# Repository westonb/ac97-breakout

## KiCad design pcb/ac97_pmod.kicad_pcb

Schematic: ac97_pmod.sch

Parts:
J101, J102, J103, J104: mounting-hole-nc; M3-small-mounting-hole

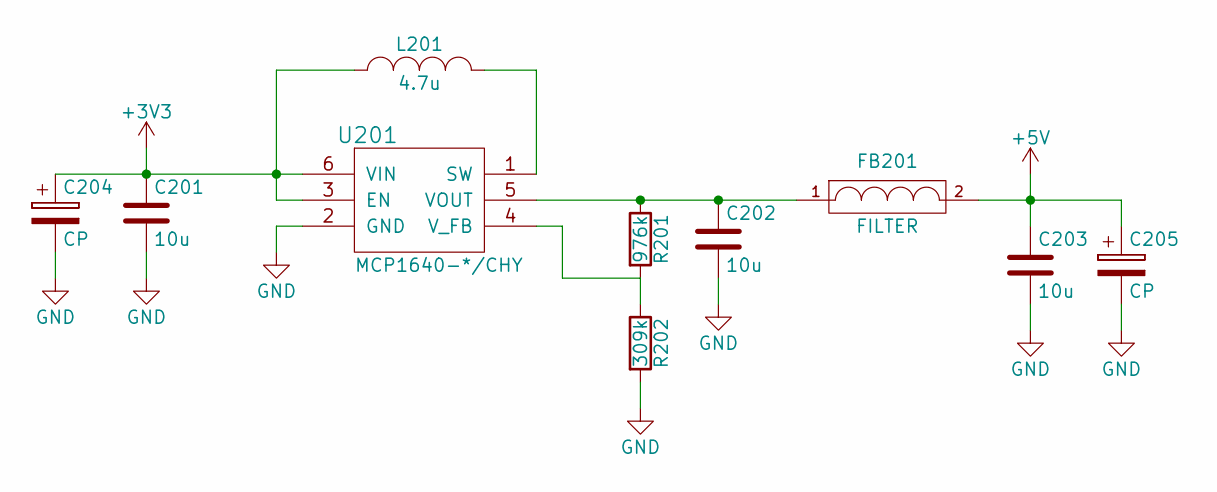
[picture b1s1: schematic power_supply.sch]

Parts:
C201, C202, C203: 10u; C_0805
C204, C205: CP; CP_Radial_D6.3mm_P2.50mm
FB201: FILTER; SMD-0805
L201: 4.7u; SMD-1008
R201: 976k; R_0805
R202: 309k; R_0805
U201: MCP1640-*/CHY; SOT-23-6

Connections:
+3V3: C201.1, C204.1, L201.1, U201.3 (EN), U201.6 (VIN); also elsewhere on the board
+5V: C203.1, C205.1, FB201.2; also elsewhere on the board
GND: C201.2, C202.2, C203.2, C204.2, C205.2, R202.2, U201.2 (GND); also elsewhere on the board
unnamed: C202.1, FB201.1, R201.1, U201.5 (VOUT)
unnamed: L201.2, U201.1 (SW)
unnamed: R201.2, R202.1, U201.4 (V_FB)

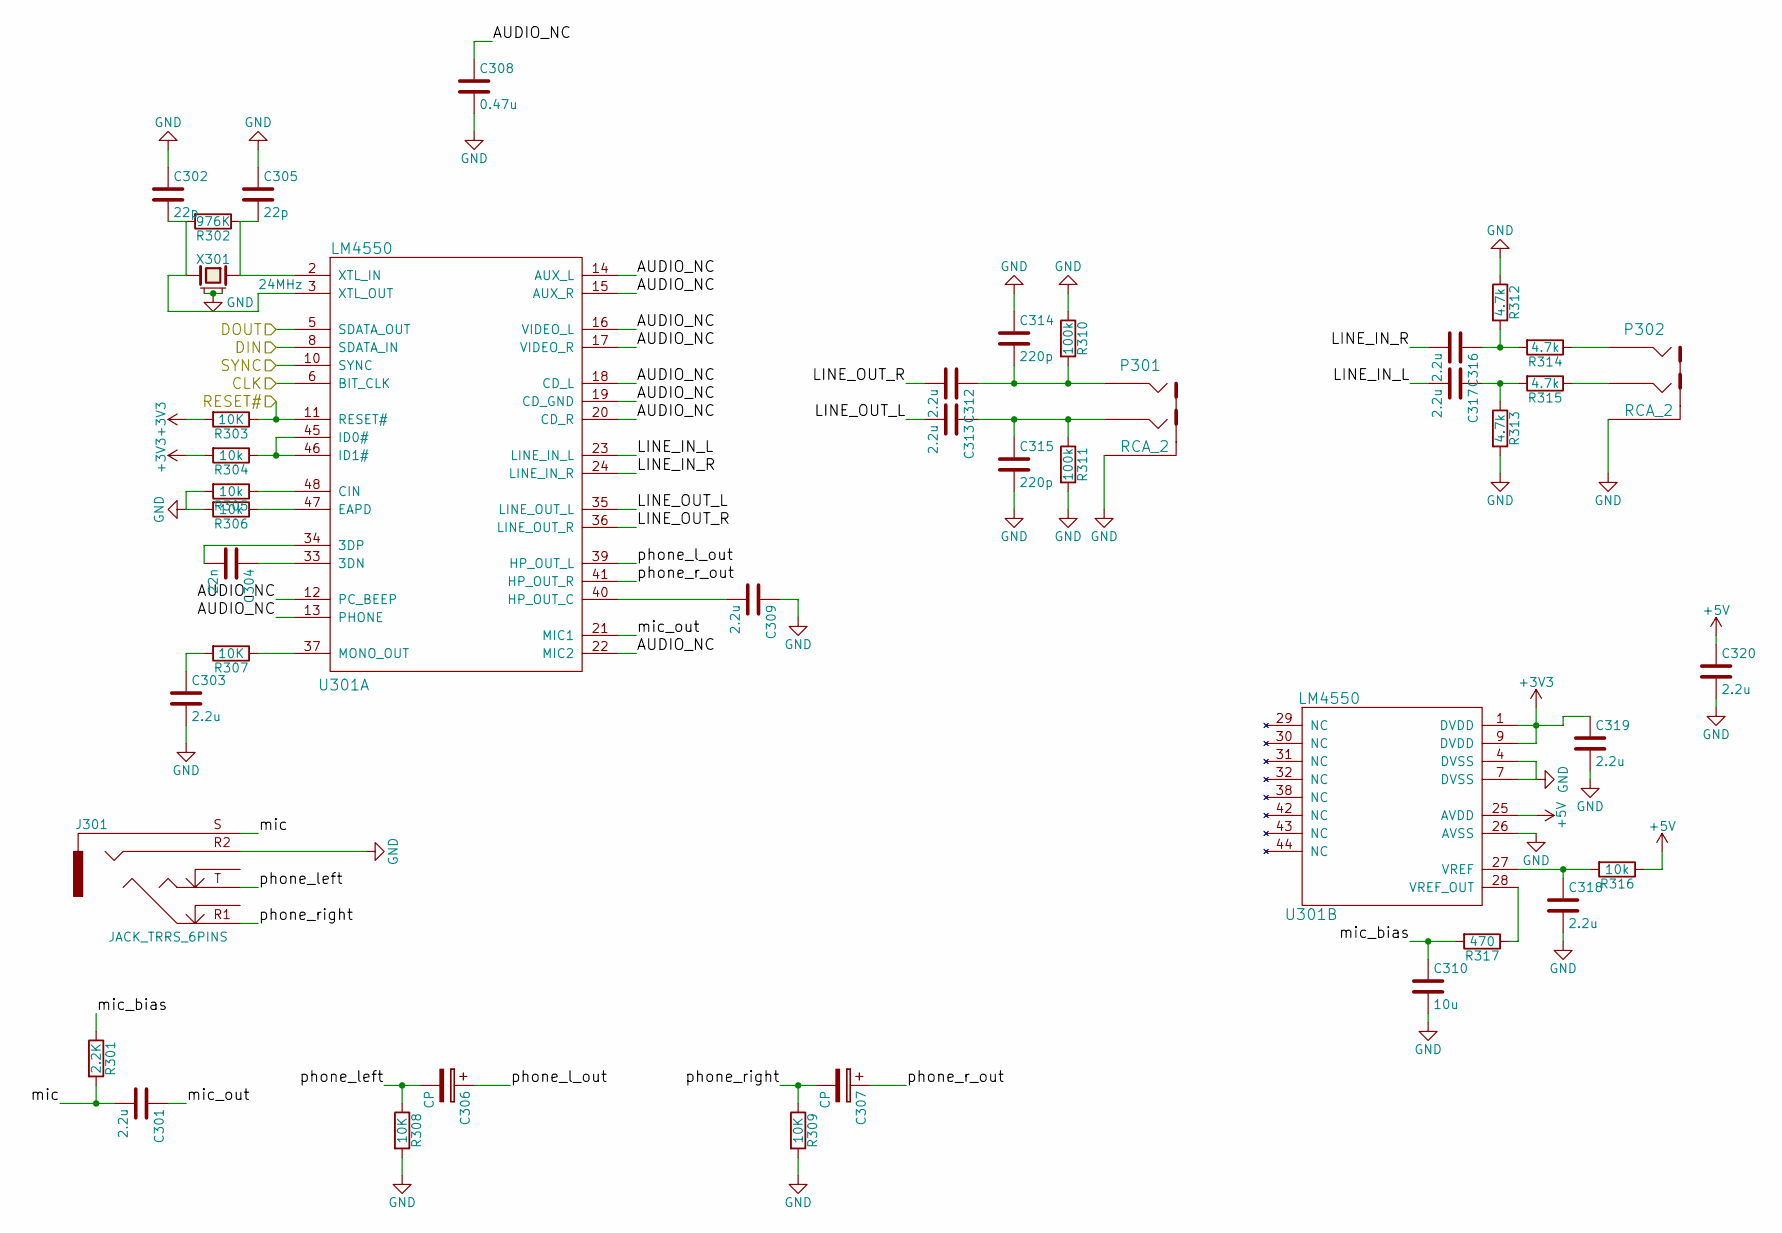
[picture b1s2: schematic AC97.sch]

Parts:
C301, C303, C309, C312, C313, C316, C317, C318, C319, C320: 2.2u; C_0805
C302, C305: 22p; C_0805
C304: 22n; C_0805
C306, C307: CP; CP_Radial_D6.3mm_P2.50mm
C308: 0.47u; C_0805
C310: 10u; C_0805
C314, C315: 220p; C_0805
J301: JACK_TRRS_6PINS; SJ-4351_X-SMT
P301, P302: RCA_2; RCJ-222x
R301: 2.2K; R_0805
R302: 976K; R_0805
R303, R307, R308, R309: 10K; R_0805
R304, R305, R306, R316: 10k; R_0805
R310, R311: 100k; R_0805
R312, R313, R314, R315: 4.7k; R_0805
R317: 470; R_0805
U301: LM4550; LQFP-48_7x7mm_Pitch0.5mm
X301: 24MHz; Crystal_6.0x3.6

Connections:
+3V3: C319.1, R303.2, R304.2, U301.1 (DVDD), U301.9 (DVDD); also elsewhere on the board
+5V: C320.1, R316.1, U301.25 (AVDD); also elsewhere on the board
/AC97/AUDIO_NC: C308.1, U301.12 (PC_BEEP), U301.13 (PHONE), U301.14 (AUX_L), U301.15 (AUX_R), U301.16 (VIDEO_L), U301.17 (VIDEO_R), U301.18 (CD_L), U301.19 (CD_GND), U301.20 (CD_R), U301.22 (MIC2)
/AC97/CLK: U301.6 (BIT_CLK); also elsewhere on the board
/AC97/DIN: U301.8 (SDATA_IN); also elsewhere on the board
/AC97/DOUT: U301.5 (SDATA_OUT); also elsewhere on the board
/AC97/LINE_IN_L: C317.2, U301.23 (LINE_IN_L)
/AC97/LINE_IN_R: C316.2, U301.24 (LINE_IN_R)
/AC97/LINE_OUT_L: C313.2, U301.35 (LINE_OUT_L)
/AC97/LINE_OUT_R: C312.2, U301.36 (LINE_OUT_R)
/AC97/SYNC: U301.10 (SYNC); also elsewhere on the board
/AC97/mic: C301.2, J301.1, R301.2
/AC97/mic_bias: C310.1, R301.1, R317.2
/AC97/mic_out: C301.1, U301.21 (MIC1)
/AC97/phone_l_out: C306.1, U301.39 (HP_OUT_L)
/AC97/phone_left: C306.2, J301.2, R308.1
/AC97/phone_r_out: C307.1, U301.41 (HP_OUT_R)
/AC97/phone_right: C307.2, J301.3, R309.1
/PMOD Connector/RESET: R303.1, U301.11 (RESET#); also elsewhere on the board
GND: C302.1, C303.2, C305.1, C308.2, C309.1, C310.2, C314.1, C315.2, C318.2, C319.2, C320.2, J301.4, P301.1, P302.1, R305.2, R306.2, R308.2, R309.2, R310.1, R311.2, R312.1, R313.2, U301.4 (DVSS), U301.7 (DVSS), U301.26 (AVSS), X301.2, X301.4; also elsewhere on the board
unnamed: C302.2, R302.2, U301.3 (XTL_OUT), X301.3
unnamed: C303.1, R307.2
unnamed: C304.1, U301.33 (3DN)
unnamed: C304.2, U301.34 (3DP)
unnamed: C305.2, R302.1, U301.2 (XTL_IN), X301.1
unnamed: C309.2, U301.40 (HP_OUT_C)
unnamed: C312.1, C314.2, P301.3, R310.2
unnamed: C313.1, C315.1, P301.2, R311.1
unnamed: C316.1, R312.2, R314.2
unnamed: C317.1, R313.1, R315.2
unnamed: C318.1, R316.2, U301.27 (VREF)
unnamed: P302.2, R315.1
unnamed: P302.3, R314.1
unnamed: R304.1, U301.45 (ID0#), U301.46 (ID1#)
unnamed: R305.1, U301.48 (CIN)
unnamed: R306.1, U301.47 (EAPD)
unnamed: R307.1, U301.37 (MONO_OUT)
unnamed: R317.1, U301.28 (VREF_OUT)

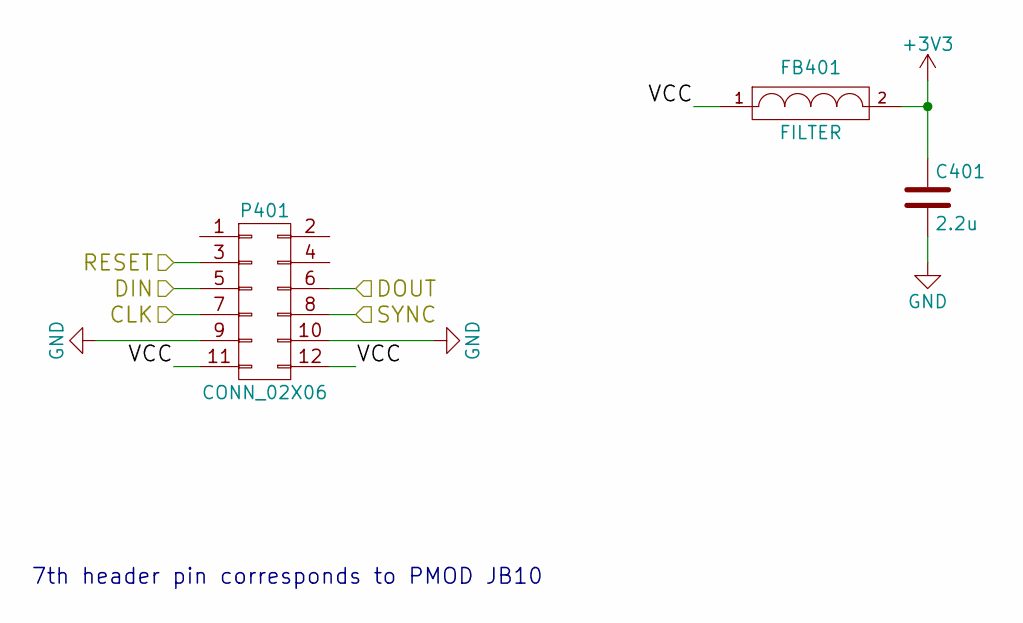
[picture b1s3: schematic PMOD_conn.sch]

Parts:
C401: 2.2u; C_0805
FB401: FILTER; SMD-0805
P401: CONN_02X06; Pin_Header_Straight_2x06

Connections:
+3V3: C401.1, FB401.2; also elsewhere on the board
/AC97/CLK: P401.7; also elsewhere on the board
/AC97/DIN: P401.5; also elsewhere on the board
/AC97/DOUT: P401.6; also elsewhere on the board
/AC97/SYNC: P401.8; also elsewhere on the board
/PMOD Connector/RESET: P401.3; also elsewhere on the board
/PMOD Connector/VCC: FB401.1, P401.11, P401.12
GND: C401.2, P401.9, P401.10; also elsewhere on the board

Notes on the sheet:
7th header pin corresponds to PMOD JB10

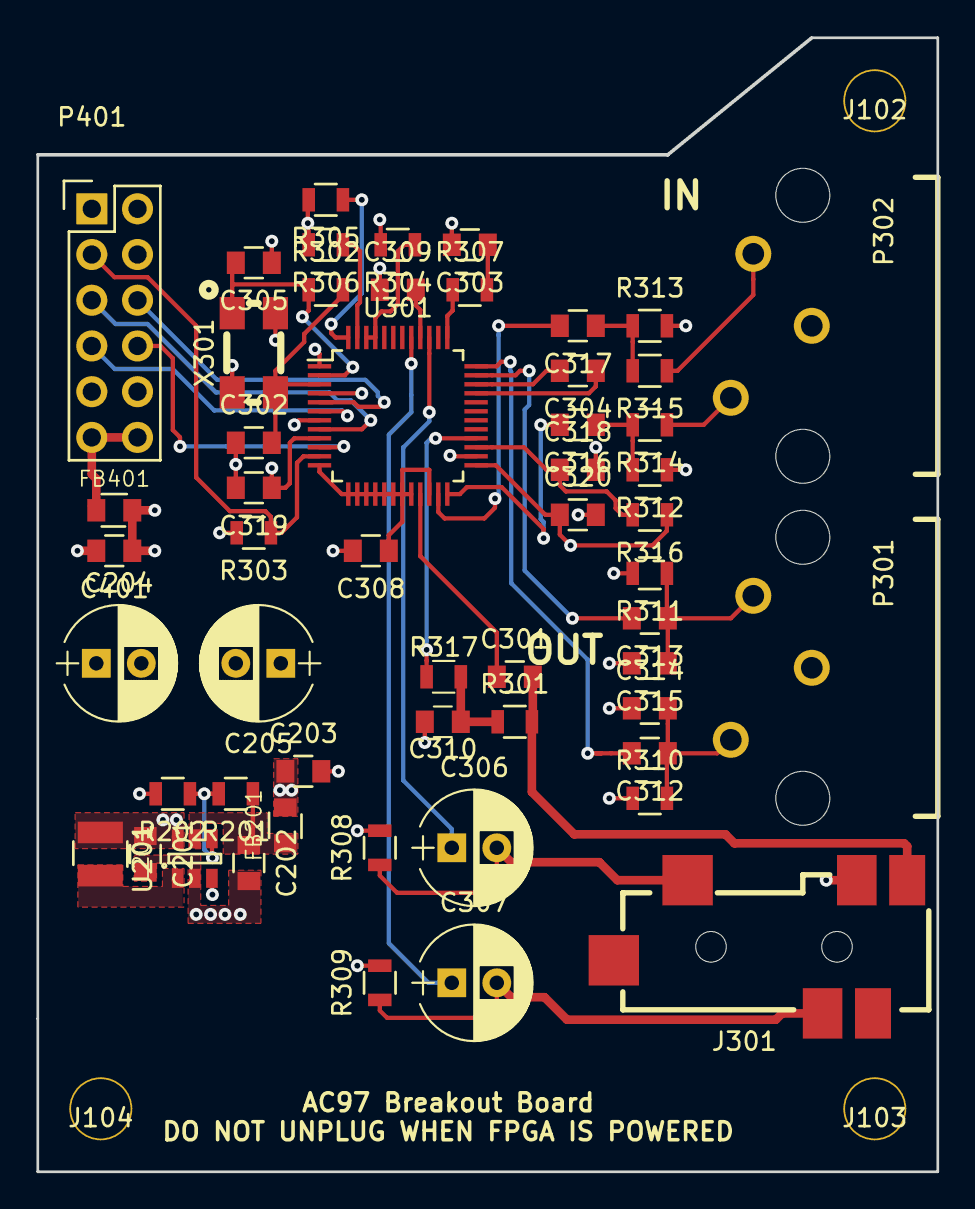
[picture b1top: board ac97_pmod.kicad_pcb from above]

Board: 4 copper layers, 50.0 x 63.0 mm, 57 parts (0 on the bottom side), 42 nets.

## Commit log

2016-09-07 first git commit
2016-11-23 added schematic
2017-11-03 replaced ceramic DC blocking caps with electrolytics
2017-11-21 fixed bad schematic symbols due to new kicad version
2018-10-01 updated symbol table
